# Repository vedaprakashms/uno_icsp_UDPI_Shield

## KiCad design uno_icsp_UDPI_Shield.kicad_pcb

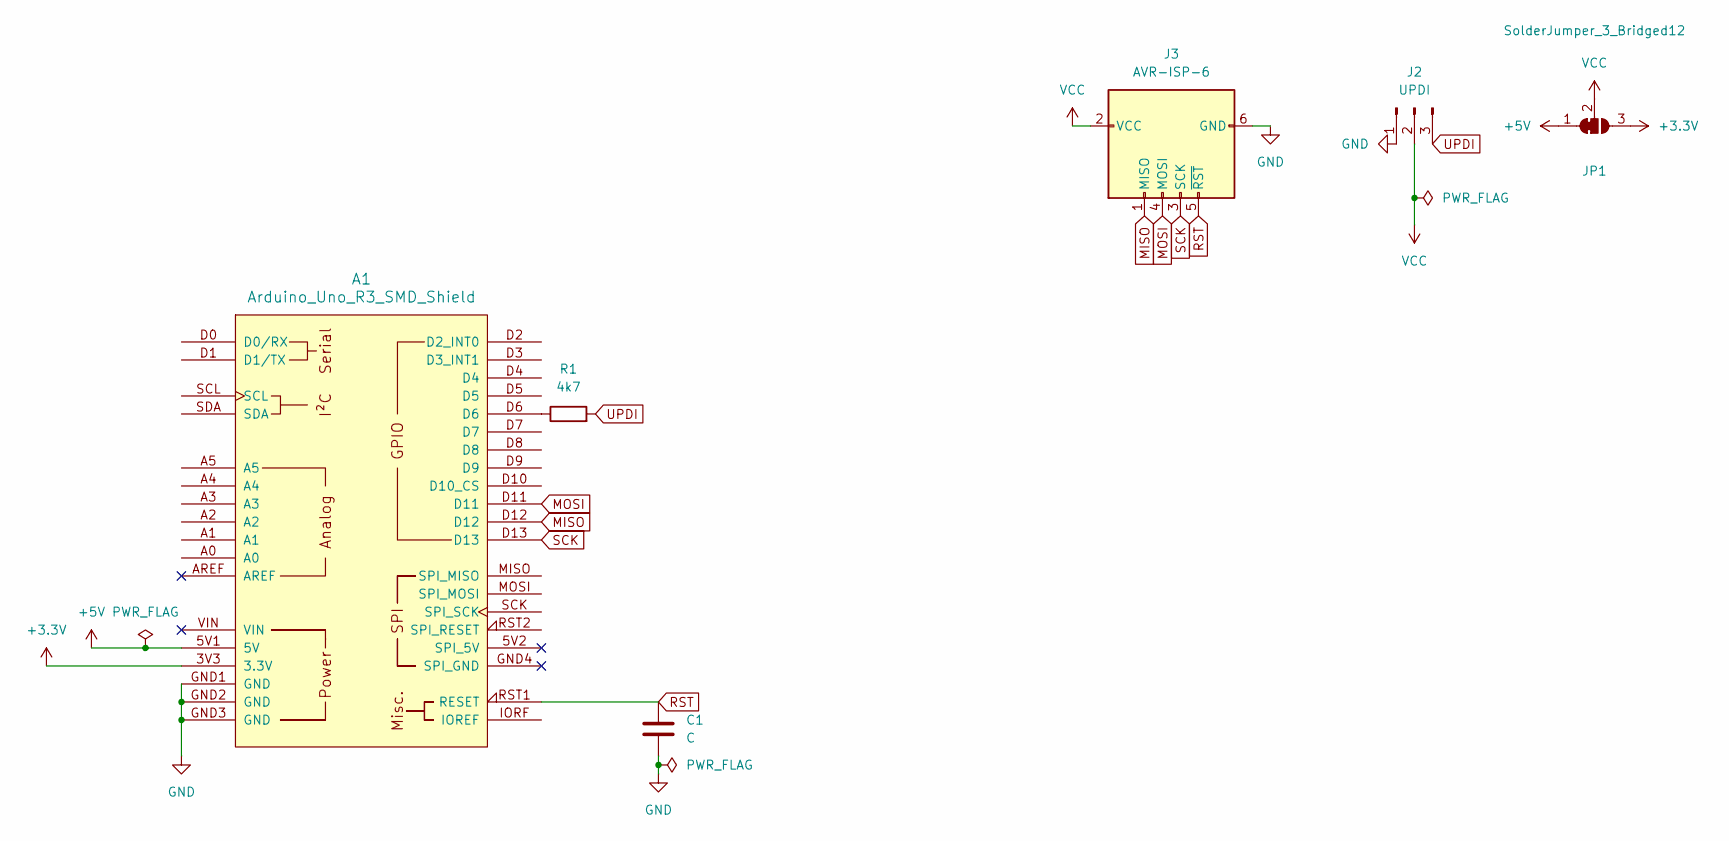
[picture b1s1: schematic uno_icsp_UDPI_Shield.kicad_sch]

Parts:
A1: Arduino_Uno_R3_SMD_Shield; Arduino_Uno_R3_Shield
C1: C; C_0805_2012Metric
J2: UPDI; PinSocket_1x03_P2.54mm_Vertical
J3: AVR-ISP-6; PinSocket_2x03_P2.54mm_Vertical
JP1: SolderJumper_3_Bridged12; SolderJumper-3_P1.3mm_Bridged12_Pad1.0x1.5mm_NumberLabels
R1: 4k7; R_0805_2012Metric_Pad1.20x1.40mm_HandSolder

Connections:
+3.3V: A1.3V3 (3.3V), JP1.3 (B)
+5V: A1.5V1 (5V), JP1.1 (A)
GND: A1.GND1 (GND), A1.GND2 (GND), A1.GND3 (GND), C1.2, J2.1, J3.6 (GND)
MISO: A1.D12, J3.1 (MISO)
MOSI: A1.D11, J3.4 (MOSI)
unnamed: A1.D6, R1.1
RST: A1.RST1 (RESET), C1.1, J3.5 (~RST)
SCK: A1.D13, J3.3 (SCK)
UPDI: J2.3, R1.2
VCC: J2.2, J3.2 (VCC), JP1.2 (C)

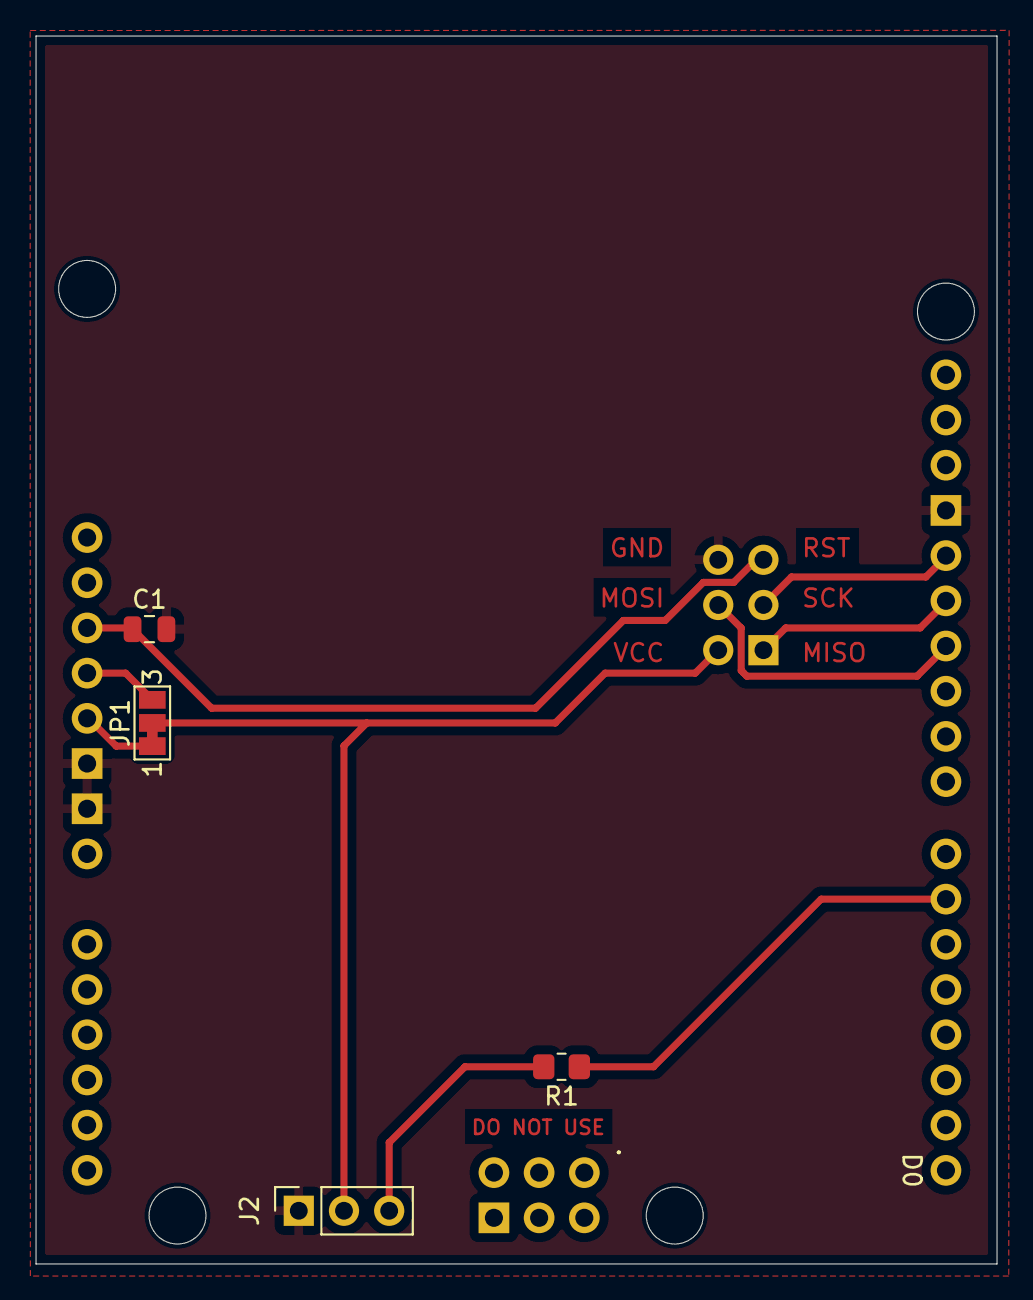
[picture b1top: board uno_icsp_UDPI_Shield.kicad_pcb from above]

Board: 2 copper layers, 54.0 x 69.0 mm, 6 parts (1 on the bottom side), 10 nets.
